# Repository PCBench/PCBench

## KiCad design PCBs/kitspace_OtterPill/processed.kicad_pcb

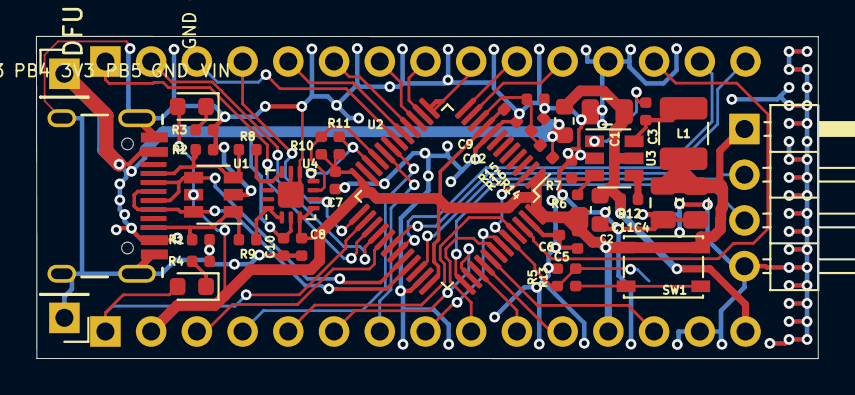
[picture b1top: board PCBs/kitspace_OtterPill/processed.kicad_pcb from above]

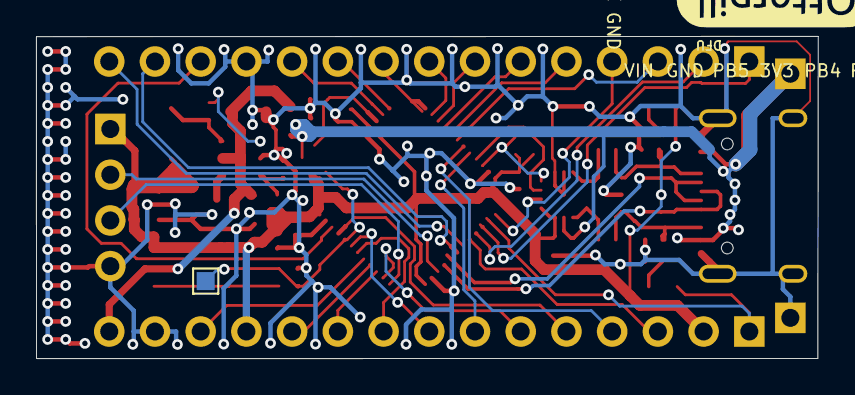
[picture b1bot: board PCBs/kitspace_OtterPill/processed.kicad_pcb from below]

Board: 2 copper layers, 43.4 x 17.9 mm, 45 parts (3 on the bottom side), 48 nets.

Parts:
C1, C4, C11: 10u 25V; C_0805_2012Metric
C2: 100n 50V; C_0603_1608Metric
C3, C5, C6, C7, C8, C9, C10, C12: 100n 50V; C_0402_1005Metric
D1: LED RED; LED_0603_1608Metric
D2: LED GREEN; LED_0603_1608Metric
G1: LOGO; otter_laying_3411
G2: LOGO; otterpill_126x46
J1: USB-c; USB-C 16Pin
J2: VBUS; PinHeader_1x01_P2.54mm_Vertical
J3: 1; PinHeader_1x15_P2.54mm_Vertical
J4: 2; PinHeader_1x15_P2.54mm_Vertical
J5: SWD; PinHeader_1x04_P2.54mm_Horizontal
J6: GND; PinHeader_1x01_P2.54mm_Vertical
J7: PAD; TestPoint_Pad_1.0x1.0mm
L1: 4u7; L_1210_3225Metric
R1, R2: DNP; R_0402_1005Metric
R3, R4, R5, R10, R11: 3k3; R_0402_1005Metric
R6, R12, R14: 100k; R_0402_1005Metric
R7, R15: 22k; R_0402_1005Metric
R8, R9: 0; R_0402_1005Metric
R13: 100; R_0402_1005Metric
R16: 1; R_0603_1608Metric
SW1: DFU; SW_SPST_PTS810
U1: USBLC6-4; SOT-23-6
U2: STM32F072C8Tx; LQFP-48_7x7mm_P0.5mm
U3: SY8201; SOT-23-6
U4: FUSB302BMPX; WQFN-14-1EP_2.5x2.5mm_P0.5mm_EP1.45x1.45mm

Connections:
+3V3: C4.1, C5.1, C6.1, C7.1, C8.1, C9.1, C11.1, D1.2, J4.2, J4.12, J5.1, L1.2, R6.1, R10.1, R11.1, SW1.2, U1.5, U2.1, U2.9, U2.24, U2.36, U2.48, U4.3, U4.4
CC1: J1.A5, R2.2, R8.1, U1.3
CC2: J1.B5, R1.2, R9.1, U1.1
GND: C1.2, C2.2, C4.2, C5.2, C6.2, C7.2, C8.2, C9.2, C10.2, C11.2, C12.2, J1.A1, J1.A12, J1.B1, J1.B12, J1.S1, J3.12, J4.14, J5.4, J6.1, R1.1, R2.1, R3.2, R4.2, R5.2, R7.2, R15.2, U1.2, U2.8, U2.23, U2.35, U2.47, U3.2, U4.8, U4.9, U4.15
INT_N: J3.4, U2.25, U4.5
unnamed: C3.1, U3.1
unnamed: C3.2, L1.1, U3.6
unnamed: D1.1, R3.1
unnamed: D2.1, R4.1
unnamed: J7.1, R5.1, R13.2, U2.2, U2.44
unnamed: R6.2, R7.1, U3.3
unnamed: R8.2, U4.10, U4.11
unnamed: R9.2, U4.1, U4.14
unnamed: R12.2, U3.4
unnamed: R13.1, SW1.1
PA0: C12.1, R14.2, R15.1, U2.10
PA1: J3.11, U2.11
PA2: J3.10, U2.12
PA3: J3.9, U2.13
PA4: J3.8, U2.14
PA5: J3.7, U2.15
PA6: J3.6, U2.16
PA7: J3.5, U2.17
PA8: J4.3, U2.29
PA9: J3.15, U2.30
PA10: J3.14, U2.31
PA15: J4.6, U2.38
PB0: J3.3, U2.18
PB1: J4.4, U2.19
PB2: J4.7, U2.20
PB3: J4.10, U2.39
PB4: J4.11, U2.40
PB5: J4.13, U2.41
PB6: J4.9, U2.42
PB7: J4.8, U2.43
PB8: J4.5, U2.45
PB9: J3.13, U2.46
PB13: D2.2, J4.1, U2.26
PB14: J3.1, U2.27
PB15: J3.2, U2.28
SCL: R10.2, U2.21, U4.6
SDA: R11.2, U2.22, U4.7
SWCLK: J5.3, U2.37
SWDIO: J5.2, U2.34
USB_N: J1.A7, J1.B7, U1.4, U2.32
USB_P: J1.A6, J1.B6, U1.6, U2.33
VBUS: C10.1, J1.A4, J1.A9, J1.B4, J1.B9, J2.1, R14.1, R16.1, U4.2
VIN: C1.1, C2.1, J4.15, R12.1, R16.2, U3.5

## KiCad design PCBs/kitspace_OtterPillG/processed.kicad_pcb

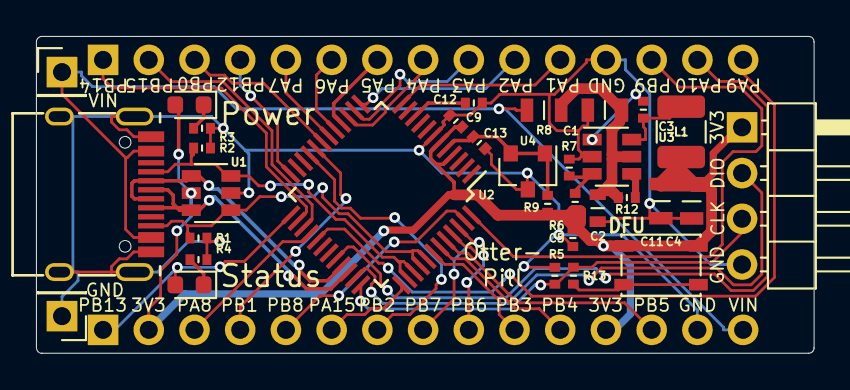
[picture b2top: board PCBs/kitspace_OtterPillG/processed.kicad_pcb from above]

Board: 2 copper layers, 43.2 x 17.6 mm, 34 parts (0 on the bottom side), 44 nets.

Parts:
C1, C4, C11: 10u 25V; C_0805
C2: 100n 50V; C_0603
C3, C5, C9, C12, C13: 100n 50V; C_0402
D1: LED RED; LED_0603_1608Metric
D2: LED GREEN; LED_0603_1608Metric
J1: USB-c; USB-C 16Pin
J2: VBUS; PinHeader_1x01_P2.54mm_Vertical
J3: 1; PinHeader_1x15_P2.54mm_Vertical
J4: 2; PinHeader_1x15_P2.54mm_Vertical
J5: SWD; PinHeader_1x04_P2.54mm_Horizontal
J6: GND; PinHeader_1x01_P2.54mm_Vertical
L1: 4u7; L_1210_3225Metric
R1, R2: DNP; R_0402
R3, R4, R5: 3k3; R_0402
R6, R12: 100k; R_0402
R7: 22k; R_0402
R8: 1; R_0805
R9, R13: 100; R_0402
SW1: DFU; SW_SPST_PTS810
U1: USBLC6-4; SOT-23-6
U2: STM32G071C8Tx; TQFP-48_7x7mm_P0.5mm
U3: SY8201; SOT-23-6
U4: CJ431; SOT-23

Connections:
+3V3: C4.1, C5.1, C9.1, C11.1, D1.2, J4.2, J4.12, J5.1, L1.2, R6.1, R9.1, SW1.2, U1.5, U2.4, U2.6
CC1: J1.A5, R2.2, U1.3, U2.38, U2.39
CC2: J1.B5, R1.2, U1.1, U2.40, U2.41
GND: C1.2, C2.2, C4.2, C5.2, C9.2, C11.2, C12.2, C13.2, J1.A1, J1.B1, J1.S1, J3.12, J4.14, J5.4, J6.1, R1.1, R2.1, R3.2, R4.2, R5.2, R7.2, U1.2, U2.7, U3.2, U4.3
unnamed: C1.1, C2.1, R8.2, R12.1, U3.5
unnamed: C3.1, U3.1
unnamed: C3.2, L1.1, U3.6
unnamed: C12.1, U2.10
unnamed: D1.1, R3.1
unnamed: D2.1, R4.1
unnamed: R6.2, R7.1, U3.3
unnamed: R12.2, U3.4
unnamed: R13.1, SW1.1
PA1: J3.11, U2.12
PA2: J3.10, U2.13
PA3: J3.9, U2.14
PA4: J3.8, U2.15
PA5: J3.7, U2.16
PA6: J3.6, U2.17
PA7: J3.5, U2.18
PA8: J4.3, U2.28
PA9: J3.15, U2.29
PA10: J3.14, U2.32
PA15: J4.6, U2.37
PB0: J3.3, U2.19
PB1: J4.4, U2.20
PB2: J4.7, U2.21
PB3: J4.10, U2.42
PB4: J4.11, U2.43
PB5: J4.13, U2.44
PB6: J4.9, U2.45
PB7: J4.8, U2.46
PB8: J4.5, U2.47
PB9: J3.13, U2.48
PB12: J3.4, U2.24
PB13: D2.2, J4.1, U2.25
PB14: J3.1, U2.26
PB15: J3.2, U2.27
SWCLK: J5.3, R5.1, R13.2, U2.36
SWDIO: J5.2, U2.35
USB_N: J1.A7, J1.B7, U1.4, U2.33
USB_P: J1.A6, J1.B6, U1.6, U2.34
VIN: J1.A4, J1.B4, J2.1, J4.15, R8.1
VREF+: C13.1, R9.2, U2.5, U4.1, U4.2

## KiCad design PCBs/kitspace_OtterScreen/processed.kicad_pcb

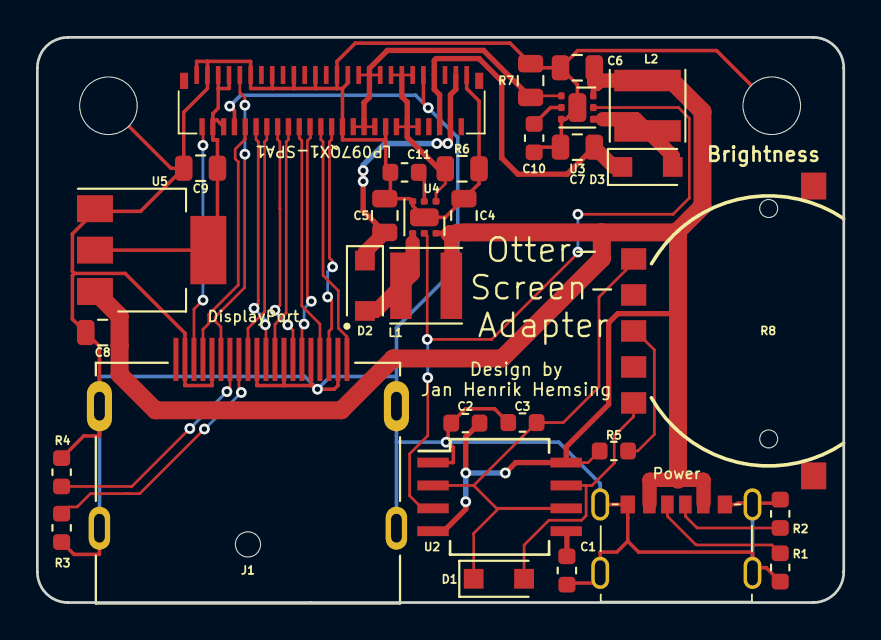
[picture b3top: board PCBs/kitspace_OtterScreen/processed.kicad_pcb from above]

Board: 2 copper layers, 44.8 x 31.4 mm, 33 parts (0 on the bottom side), 31 nets.

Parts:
C1, C2: 100n; C_0603_1608Metric
C3: 1n; C_0603_1608Metric
C4, C6: 10uF; C_0805_2012Metric
C5, C7, C8, C9: 0.47uF; C_0805_2012Metric
C10, C11: 220nF; C_0603_1608Metric
D1: D; D_SOD-123F
D2, D3: SS34; D_SOD-123F
H1, H2: MountingHole_Pad; MountingHole_3.2mm_M3
J1: 47272-0001; MOLEX_47272-0001
J2: USB-C_Power
L1, L2: 22uH; L_Taiyo-Yuden_MD-4040
R1, R2: 5K1; R_0603_1608Metric
R3, R4: 0; R_0603_1608Metric
R5: 100; R_0603_1608Metric
R6, R7: 0.8; R_0805_2012Metric
R8: RK14J12R0A09
U1: 5022505191
U2: NE555; SO-8_5.3x6.2mm_P1.27mm
U3, U4: TPS61160A; WSON-6-1EP_2x2mm_P0.65mm_EP1x1.6mm
U5: AMS1117-3.3; SOT-223-3_TabPin2

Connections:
+3V3: C9.1, U1.4, U1.5, U1.6, U1.7, U5.2
+5V: C2.1, C4.1, C6.1, C8.1, J2.2, J2.5, L1.1, L2.1, R5.1, U2.4, U2.8, U3.6, U4.6, U5.3
AUX_N: J1.17, U1.10
AUX_P: J1.15, U1.9
GND: C1.2, C2.2, C3.2, C4.2, C5.2, C6.2, C7.2, C8.2, C9.2, C10.2, C11.2, H1.1, H2.1, J1.2, J1.5, J1.8, J1.11, J1.16, J1.19, J1.S1, J1.S2, J1.S3, J1.S4, J2.1, J2.6, J2.7, R1.2, R2.2, R3.2, R4.2, R6.2, R7.2, U1.1, U1.3, U1.8, U1.11, U1.15, U1.19, U1.23, U1.27, U1.28, U1.29, U1.36, U1.43, U1.51, U2.1, U3.3, U3.7, U4.3, U4.7, U5.1
HPD: J1.18, U1.2
L0_N: J1.10, U1.12
L0_P: J1.12, U1.14
L1_N: J1.7, U1.16
L1_P: J1.9, U1.18
L2_N: J1.4, U1.20
L2_P: J1.6, U1.22
L3_N: J1.1, U1.24
L3_P: J1.3, U1.26
LEDA1: C5.1, D2.1, U1.48, U1.49
LEDA2: C7.1, D3.1, U1.45, U1.46
LEDC1: R6.1, U1.37, U1.38, U1.39, U1.40, U1.41, U1.42, U4.1
LEDC2: R7.1, U1.30, U1.31, U1.32, U1.33, U1.34, U1.35, U3.1
unnamed: C1.1, U2.5
unnamed: C3.1, D1.1, R8.1, U2.2, U2.6
unnamed: C10.1, U3.2
unnamed: C11.1, U4.2
unnamed: D1.2, R8.2, U2.7
unnamed: D2.2, L1.2, U4.4
unnamed: D3.2, L2.2, U3.4
unnamed: J1.13, R3.1
unnamed: J1.14, R4.1
unnamed: J2.3, R1.1
unnamed: J2.4, R2.1
unnamed: R5.2, R8.3
PWM: U2.3, U3.5, U4.5

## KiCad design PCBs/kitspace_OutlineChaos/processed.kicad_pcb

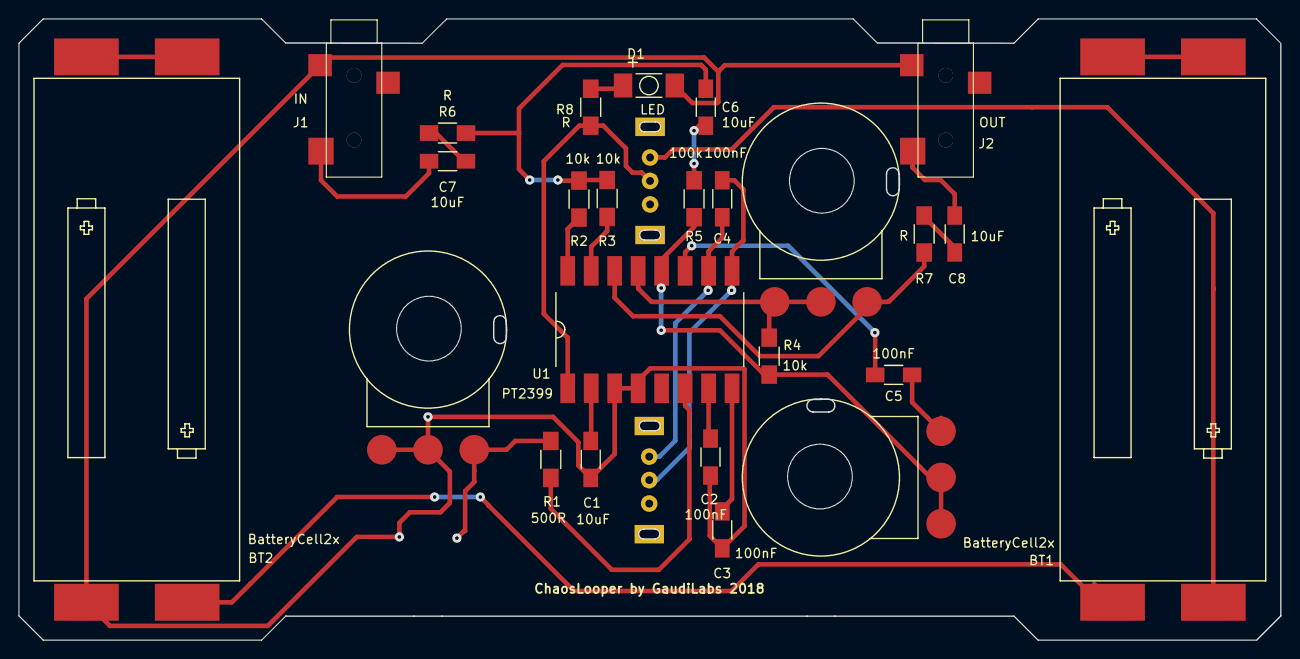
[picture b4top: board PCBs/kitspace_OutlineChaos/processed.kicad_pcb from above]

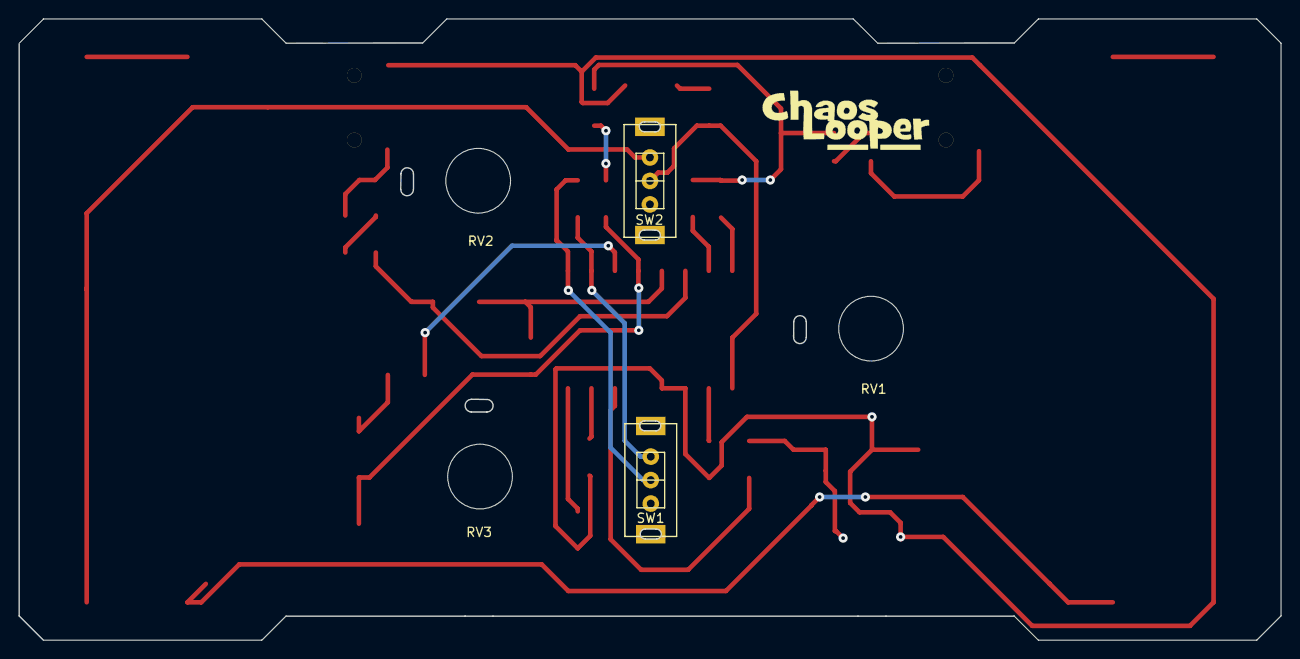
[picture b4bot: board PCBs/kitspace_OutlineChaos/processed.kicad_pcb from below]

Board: 2 copper layers, 136.5 x 67.2 mm, 27 parts (5 on the bottom side), 27 nets.

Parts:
BT1, BT2: BatteryCell2x; BAT_HOLDER_AAA_DOUBLE
C1, C6, C7, C8: 10uF; C_1206_HandSoldering
C2, C3, C4, C5: 100nF; C_1206_HandSoldering
D1: LED; TOPLED_R
J1: IN; PLUG3_5_SwitchCraft_2B
J2: OUT; PLUG3_5_SwitchCraft_2B
R1: 500R; R_1206_HandSoldering
R2, R3, R4: 10k; R_1206_HandSoldering
R5: 100k; R_1206_HandSoldering
R6, R7, R8: R; R_1206_HandSoldering
RV1: SPEED_POT; POTI_PCB
RV2: VOL_POT; POTI_PCB
RV3: POT; POTI_PCB
SW1, SW2: Switch; SWITCH_SLIDE
U1: PT2399; DIL16_SMD

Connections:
GND: BT2.4, C1.2, C2.1, C3.1, D1.1, J1.1, J2.1, RV1.2, RV1.3, U1.3, U1.4
unnamed: BT1.1, SW2.1
unnamed: BT1.2, BT1.3
unnamed: BT1.4, BT2.1
unnamed: BT2.2, BT2.3
unnamed: C1.1, U1.2
unnamed: C2.2, U1.7
unnamed: C3.2, U1.8
unnamed: C4.1, SW1.2, U1.9
unnamed: C4.2, SW1.1, U1.10
unnamed: C5.1, RV3.1
unnamed: C5.2, U1.11
unnamed: C6.1, R2.1, R3.1, R6.2
unnamed: C6.2, R5.1
unnamed: C7.1, J1.3
unnamed: C7.2, R6.1
unnamed: C8.1, J2.3
unnamed: C8.2, R7.1
unnamed: D1.2, R8.1
unnamed: R1.1, RV1.1
unnamed: R1.2, U1.6
unnamed: R2.2, U1.16
unnamed: R3.2, U1.15
unnamed: R4.1, R5.2, RV3.2, RV3.3, U1.12
unnamed: R4.2, RV2.2, RV2.3, U1.13
unnamed: R7.2, RV2.1, U1.14
VCC: R8.2, SW2.2, U1.1

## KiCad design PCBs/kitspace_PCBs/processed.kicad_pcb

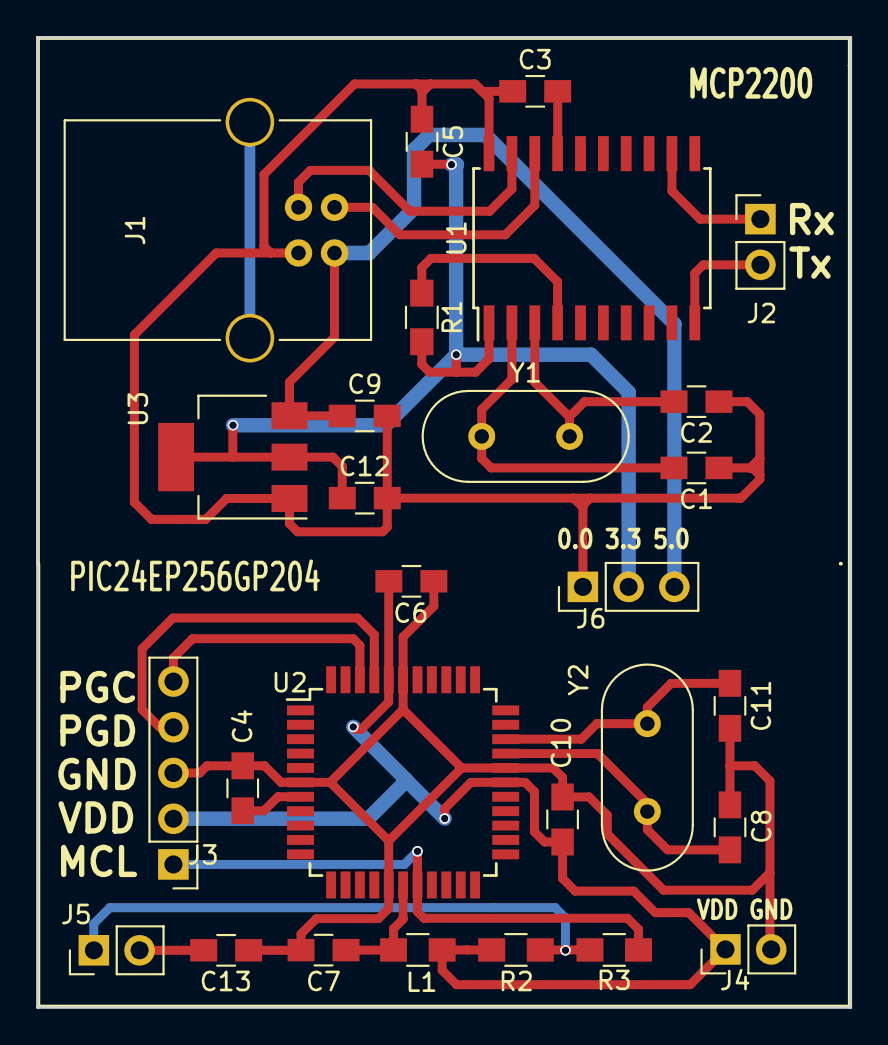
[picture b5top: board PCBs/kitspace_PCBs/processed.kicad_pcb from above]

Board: 2 copper layers, 45.2 x 53.9 mm, 28 parts (0 on the bottom side), 22 nets.

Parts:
C1, C2, C8, C11: 15p; C_0805_HandSoldering
C3, C5, C6, C7, C10, C13: 0.1u; C_0805_HandSoldering
C4, C12: 10u; C_0805_HandSoldering
C9: 1u; C_0805_HandSoldering
J1: USB; USB_B
J2: Tx_Rx; Pin_Header_Straight_1x02_Pitch2.54mm
J3: Programmer; Pin_Header_Straight_1x05_Pitch2.54mm
J4: Power; Pin_Header_Straight_1x02_Pitch2.54mm
J5: MCLR_J; Pin_Header_Straight_1x02_Pitch2.54mm
J6: Power; Pin_Header_Straight_1x03_Pitch2.54mm
L1: 10uH; L_0805_HandSoldering
R1: 4.7k; R_0805_HandSoldering
R2: 9k8; R_0805_HandSoldering
R3: 330; R_0805_HandSoldering
U1: MCP2200; SOIC-20W_7.5x12.8mm_Pitch1.27mm
U2: PIC24EP64GP204; TQFP-44_10x10mm_Pitch0.8mm
U3: LM1117-3.3; SOT-223
Y1, Y2: Crystal; Crystal_HC49-4H_Vertical

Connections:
D+: J1.3, U1.19
D-: J1.2, U1.18
GND: C4.2, C6.1, C7.2, C8.2, C10.1, C11.2, C13.2, J3.3, J4.2, U2.6, U2.16, U2.29, U2.39
MCLR: J3.1, R3.1, U2.18
MCL_A: J5.1, R2.1, R3.2
MCL_B: C13.1, J5.2
unnamed: C3.2, U1.17
unnamed: C4.1, U2.7
unnamed: C7.1, L1.1, U2.17
unnamed: R1.1, U1.4
OS1: C1.2, U1.2, Y1.1
OS2: C2.2, U1.3, Y1.2
OSC1: C8.1, U2.30, Y2.1
OSC2: C11.1, U2.31, Y2.2
PGC: J3.5, U2.42
PGD: J3.4, U2.41
Rx: J2.1, U1.12
Tx: J2.2, U1.10
V+: C5.2, C12.1, J6.2, R1.2, U1.1, U3.2, U3.4
V-: C1.1, C2.1, C3.1, C5.1, C9.2, C12.2, J1.4, J6.1, U1.20, U3.1
VBus: C9.1, J1.1, J6.3, U3.3
VDD: C6.2, C10.2, J3.2, J4.1, L1.2, R2.2, U2.28, U2.40

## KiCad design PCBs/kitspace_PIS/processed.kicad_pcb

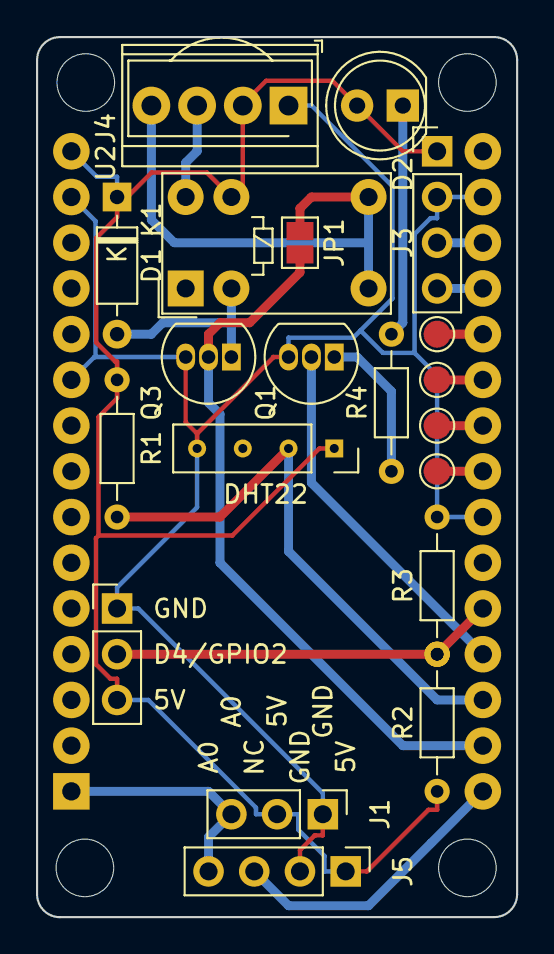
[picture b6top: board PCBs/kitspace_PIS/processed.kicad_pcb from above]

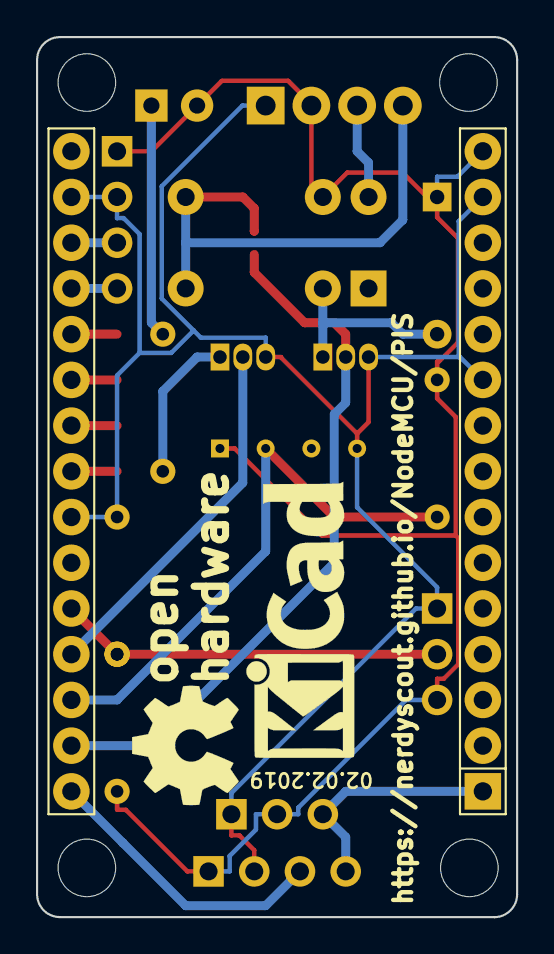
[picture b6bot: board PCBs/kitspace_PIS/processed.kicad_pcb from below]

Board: 2 copper layers, 26.7 x 48.9 mm, 24 parts (3 on the bottom side), 19 nets.

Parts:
D1: 1N4148; D_DO-35_SOD27_P7.62mm_Horizontal
D2: LED; LED_D5.0mm
J1: Capacitive Sensor; PinHeader_1x03_P2.54mm_Vertical
J2: Conn_01x03; PinHeader_1x03_P2.54mm_Vertical
J3: Serial; PinHeader_1x04_P2.54mm_Vertical
J4: Screw_Terminal_01x04; TerminalBlock_TE_282834-4_1x04_P2.54mm_Horizontal
J5: Resistive Sensor; PinHeader_1x04_P2.54mm_Vertical
JP1: NO; SolderJumper-2_P1.3mm_Open_Pad1.0x1.5mm
K1: G5V-1; Relay_SPDT_Omron_G5V-1
LOGO1: Logo_Open_Hardware_Small; OSHW-Symbol_6.7x6mm_SilkScreen
LOGO2: Logo_Open_Hardware_Small; KiCad-Logo_6mm_SilkScreen
Q1, Q3: BC547; TO-92_Inline
R1, R2, R3: 10k; R_Axial_DIN0204_L3.6mm_D1.6mm_P7.62mm_Horizontal
R4: 100; R_Axial_DIN0204_L3.6mm_D1.6mm_P7.62mm_Horizontal
TP1: CLK; TestPoint_Pad_D1.5mm
TP2: MISO; TestPoint_Pad_D1.5mm
TP3: MOSI; TestPoint_Pad_D1.5mm
TP4: CS; TestPoint_Pad_D1.5mm
U1: NodeMCU1.0(ESP-12E); NodeMCU_Amica
U2: TSOP17xx; Vishay_CAST-3Pin
U4: DHT11; PinSocket_1x04_P2.54mm_Vertical

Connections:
+5V: D1.1, D2.2, J1.2, J2.3, J3.1, J4.2, J5.1, K1.9, R1.2, R2.2, U1.15, U2.2, U4.1
A0: J1.3, J5.4, U1.1
Contact: J2.2, R2.1, R3.2, U1.26
DHT: R1.1, U1.28, U4.2
Dig: J5.3, U1.30
GND: J1.1, J2.1, J3.2, J4.1, J5.2, Q1.3, Q3.3, R3.1, U1.10, U1.14, U1.17, U1.24, U2.1, U4.4
LED: Q1.2, U1.27
unnamed: D1.2, K1.2, Q3.1
unnamed: D2.1, R4.2
unnamed: J4.3, K1.10
unnamed: J4.4, JP1.2, K1.5, K1.6, U2.3
unnamed: Q1.1, R4.1
unnamed: TP1.1, U1.23
unnamed: TP2.1, U1.22
unnamed: TP3.1, U1.21
unnamed: TP4.1, U1.20
Relay: JP1.1, Q3.2, U1.29
RxD: J3.4, U1.19
TxD: J3.3, U1.18
